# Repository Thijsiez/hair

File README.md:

# hair - Home Assistant IR blaster
The joke is that I'm bald :)

## :construction: WIP :construction:
This repo is currently a work-in-progress. I will add more information and documentation later.  
As long as this message is here, I'm open to suggestions but please do not assume anything is done or will work without issues.

## Versions
- [01](./hair-01) is a flawed prototype **DO NOT BUILD OR REFERENCE**
- [02](./hair-02) **WIP**

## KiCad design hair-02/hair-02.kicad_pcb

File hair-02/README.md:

# hair-02

The goal for 02 is to not need a USB-to-Serial interface chip like 01, lowering the total BOM cost. Another benefit of using the newer ESP32-C3 SoC, compared to the ESP8266, is that it uses the open source RISC-V instruction set.

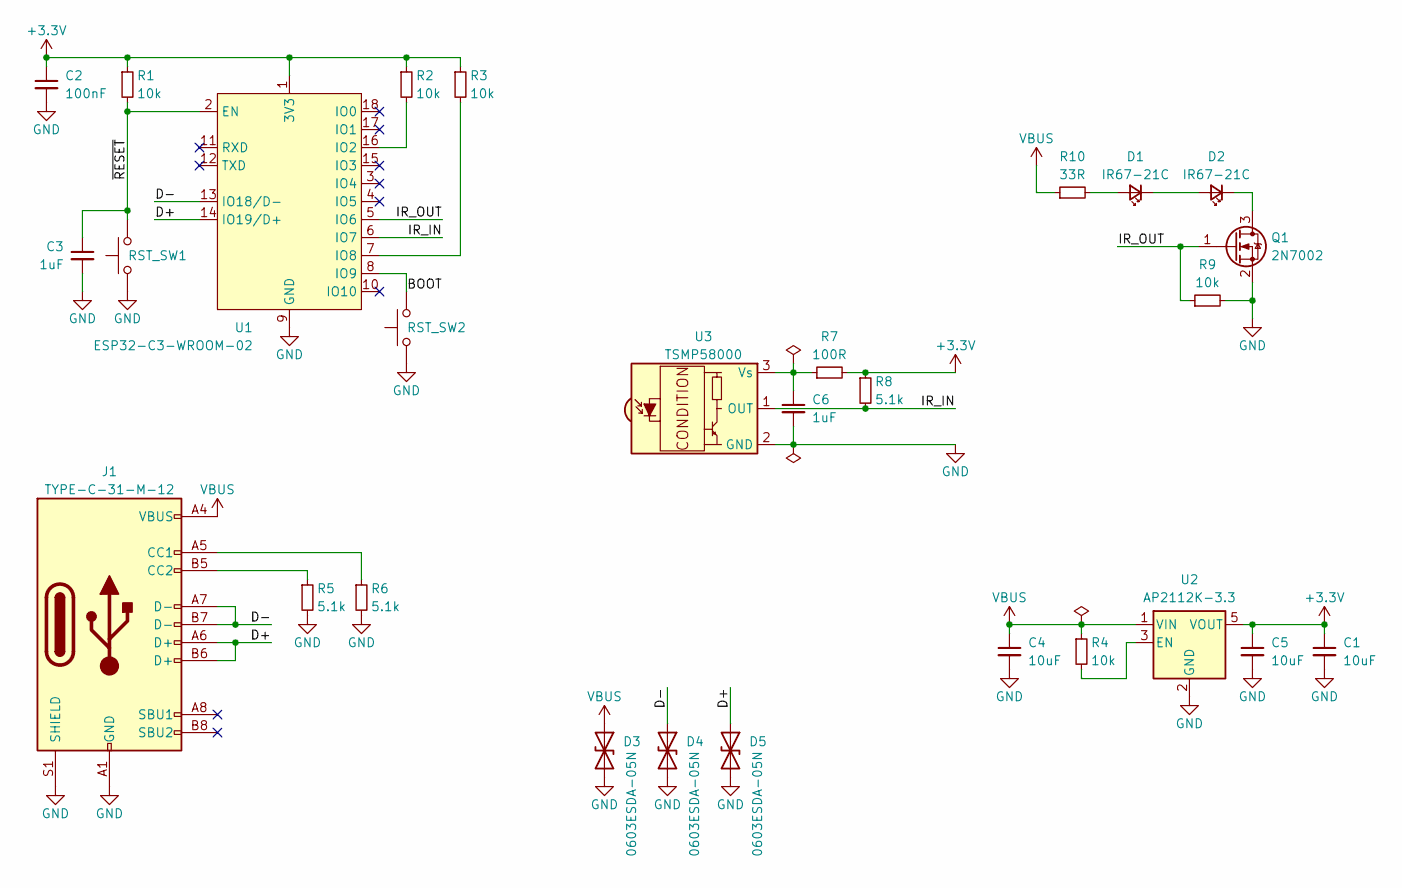
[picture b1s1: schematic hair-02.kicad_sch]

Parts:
C1, C4, C5: 10uF; C_1206_3216Metric; LCSC C13585
C2: 100nF; C_0603_1608Metric; LCSC C14663
C3, C6: 1uF; C_0805_2012Metric; LCSC C28323
D1, D2: IR67-21C; LED_Everlight_IR67-21C; LCSC C60109
D3, D4, D5: 0603ESDA-05N; D_0603_1608Metric; LCSC C316054
J1: TYPE-C-31-M-12; USB_C_Receptacle_HRO_TYPE-C-31-M-12; LCSC C165948
Q1: 2N7002; SOT-23; LCSC C414015
R1, R2, R3, R4, R9: 10k; R_0603_1608Metric; LCSC C25804
R5, R6, R8: 5.1k; R_0603_1608Metric; LCSC C23186
R7: 100R; R_0603_1608Metric; LCSC C22775
R10: 33R; R_1206_3216Metric; LCSC C144495
RST_SW1, RST_SW2: SKRK; SW_Push_SPST_NO_Alps_SKRK; LCSC C202388
U1: ESP32-C3-WROOM-02; LCSC C2934560
U2: AP2112K-3.3; SOT-23-5; LCSC C51118
U3: TSMP58000; Vishay_MINICAST-3Pin-SMD_ReverseMount; LCSC C511392

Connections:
+3V3: C1.1, C2.1, C5.1, R1.1, R2.1, R3.1, R7.2, R8.1, U1.1 (3V3), U2.5 (VOUT)
/BOOT: RST_SW2.2, U1.8 (IO9)
/D+: D5.1 (A1), J1.A6 (D+), J1.B6 (D+), U1.14 (IO19/D+)
/D-: D4.1 (A1), J1.A7 (D-), J1.B7 (D-), U1.13 (IO18/D-)
/IR_IN: R8.2, U1.6 (IO7), U3.1 (OUT)
/IR_OUT: Q1.1 (G), R9.1, U1.5 (IO6)
/~RESET: C3.1, R1.2, RST_SW1.2, U1.2 (EN)
GND: C1.2, C2.2, C3.2, C4.2, C5.2, C6.2, D3.2 (A2), D4.2 (A2), D5.2 (A2), J1.A1 (GND), J1.A12 (GND), J1.B1 (GND), J1.B12 (GND), J1.S1 (SHIELD), Q1.2 (S), R5.2, R6.2, R9.2, RST_SW1.1, RST_SW2.1, U1.9 (GND), U1.19 (GND), U2.2 (GND), U3.2 (GND)
unnamed: C6.1, R7.1, U3.3 (Vs)
unnamed: D1.1 (K), D2.2 (A)
unnamed: D1.2 (A), R10.2
unnamed: D2.1 (K), Q1.3 (D)
unnamed: J1.A5 (CC1), R6.1
unnamed: J1.B5 (CC2), R5.1
unnamed: R2.2, U1.16 (IO2)
unnamed: R3.2, U1.7 (IO8)
unnamed: R4.2, U2.3 (EN)
VBUS: C4.1, D3.1 (A1), J1.A4 (VBUS), J1.A9 (VBUS), J1.B4 (VBUS), J1.B9 (VBUS), R4.1, R10.1, U2.1 (VIN)

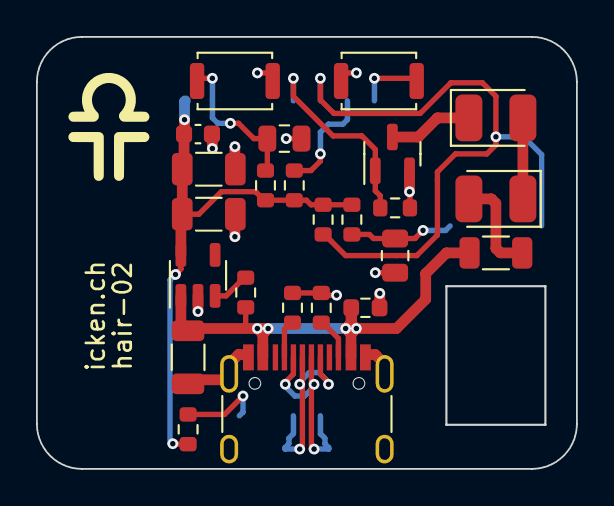
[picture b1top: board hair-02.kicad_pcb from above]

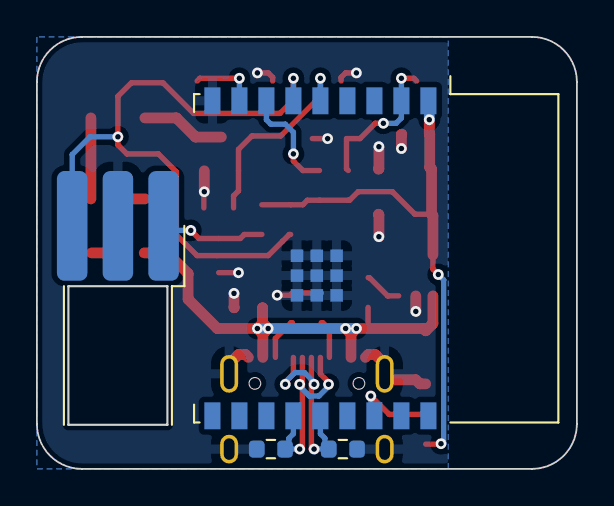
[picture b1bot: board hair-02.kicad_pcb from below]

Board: 2 copper layers, 30.0 x 24.0 mm, 28 parts (4 on the bottom side), 18 nets.

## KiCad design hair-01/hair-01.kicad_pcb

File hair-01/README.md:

# hair-01
**DO NOT USE OR REFERENCE THIS DESIGN, IT IS FLAWED AND I WILL NOT FIX IT!!**  
It's really only still here as a reference FOR ME so I don't make the same mistakes in the future.

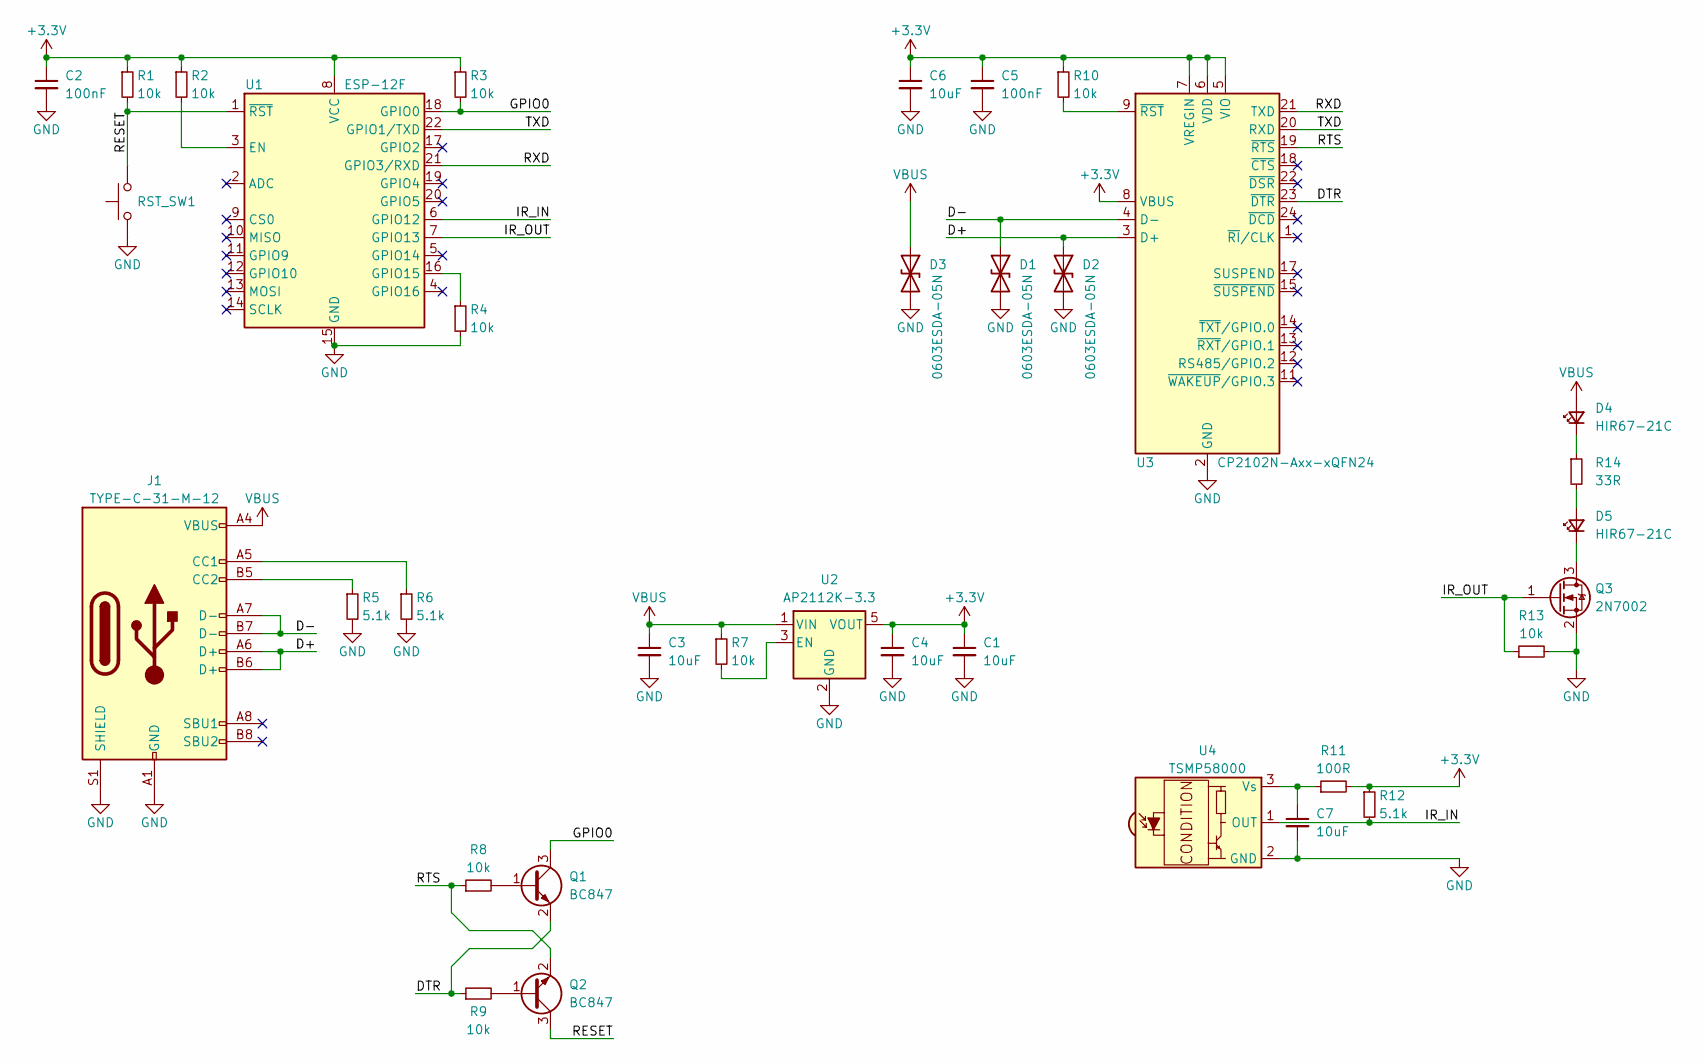
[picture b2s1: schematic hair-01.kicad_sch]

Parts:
C1, C3, C4, C6, C7: 10uF; C_1206_3216Metric; LCSC C13585
C2, C5: 100nF; C_0603_1608Metric; LCSC C14663
D1, D2, D3: 0603ESDA-05N; D_0603_1608Metric; LCSC C316054
D4, D5: HIR67-21C; LED_Everlight_HIR67-21C; LCSC C524055
J1: TYPE-C-31-M-12; USB_C_Receptacle_HRO_TYPE-C-31-M-12; LCSC C165948
Q1, Q2: BC847; SOT-23; LCSC C2150
Q3: 2N7002; SOT-23; LCSC C414015
R1, R2, R3, R4, R7, R8, R9, R10, R13: 10k; R_0603_1608Metric; LCSC C25804
R5, R6, R12: 5.1k; R_0603_1608Metric; LCSC C23186
R11: 100R; R_0603_1608Metric; LCSC C22775
R14: 33R; R_1206_3216Metric; LCSC C144495
RST_SW1: SW_Push; SW_Push_SPST_NO_Alps_SKRK; LCSC C202388
U1: ESP-12F; ESP-12E; LCSC C82891
U2: AP2112K-3.3; SOT-23-5; LCSC C51118
U3: CP2102N-Axx-xQFN24; QFN-24-1EP_4x4mm_P0.5mm_EP2.6x2.6mm; LCSC C969151
U4: TSMP58000; Vishay_MINICAST-3Pin-SMD; LCSC C511392

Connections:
+3V3: C1.1, C2.1, C4.1, C5.1, C6.1, R1.1, R2.1, R3.1, R10.1, R11.2, R12.1, U1.8 (VCC), U2.5 (VOUT), U3.5 (VIO), U3.6 (VDD), U3.7 (VREGIN), U3.8 (VBUS)
/D+: D2.1 (A1), J1.A6 (D+), J1.B6 (D+), U3.3 (D+)
/D-: D1.1 (A1), J1.A7 (D-), J1.B7 (D-), U3.4 (D-)
/DTR: Q1.2 (E), R9.1, U3.23 (~DTR)
/GPIO0: Q1.3 (C), R3.2, U1.18 (GPIO0)
/IR_IN: R12.2, U1.6 (GPIO12), U4.1 (OUT)
/IR_OUT: Q3.1 (G), R13.1, U1.7 (GPIO13)
/RESET: Q2.3 (C), R1.2, RST_SW1.2, U1.1 (~RST)
/RTS: Q2.2 (E), R8.1, U3.19 (~RTS)
/RXD: U1.21 (GPIO3/RXD), U3.21 (TXD)
/TXD: U1.22 (GPIO1/TXD), U3.20 (RXD)
GND: C1.2, C2.2, C3.2, C4.2, C5.2, C6.2, C7.2, D1.2 (A2), D2.2 (A2), D3.2 (A2), J1.A1 (GND), J1.A12 (GND), J1.B1 (GND), J1.B12 (GND), J1.S1 (SHIELD), Q3.2 (S), R4.2, R5.2, R6.2, R13.2, RST_SW1.1, U1.15 (GND), U2.2 (GND), U3.2 (GND), U3.25 (GND), U4.2 (GND)
unnamed: C7.1, R11.1, U4.3 (Vs)
unnamed: D4.1 (K), R14.1
unnamed: D5.1 (K), Q3.3 (D)
unnamed: D5.2 (A), R14.2
unnamed: J1.A5 (CC1), R6.1
unnamed: J1.B5 (CC2), R5.1
unnamed: Q1.1 (B), R8.2
unnamed: Q2.1 (B), R9.2
unnamed: R2.2, U1.3 (EN)
unnamed: R4.1, U1.16 (GPIO15)
unnamed: R7.2, U2.3 (EN)
unnamed: R10.2, U3.9 (~RST)
VBUS: C3.1, D3.1 (A1), D4.2 (A), J1.A4 (VBUS), J1.A9 (VBUS), J1.B4 (VBUS), J1.B9 (VBUS), R7.1, U2.1 (VIN)

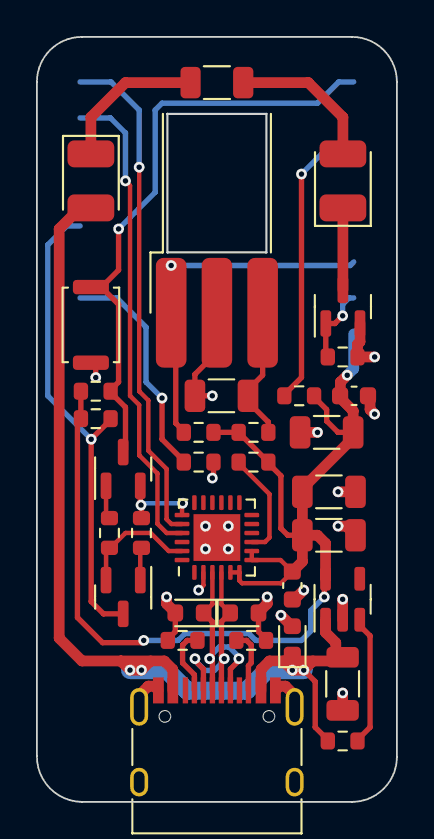
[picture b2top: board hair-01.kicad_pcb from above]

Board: 2 copper layers, 20.0 x 42.5 mm, 35 parts (1 on the bottom side), 25 nets.

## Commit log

2023-01-12 Add LICENSE
2023-01-26 hair-01: Add ESP-12F and USB-C receptacle
2023-01-26 hair-01: Add AP2112
2023-01-26 hair-01: Add reset button and auto-reset
2023-01-26 hair-01: Add CP2102N
2023-01-26 Add WIP notice
2023-01-26 hair-01: Add TSMP58000
2023-01-26 hair-01: Add IR output
2023-01-26 hair-01: Fix small naming mistake
2023-01-26 hair-01: Specify correct footprint for CP2102N
2023-01-26 hair-01: Rotate reset switch
2023-01-26 hair-01: Add footprints and start board layout
2023-01-26 hair-01: Replace reset button and more routing
2023-01-26 hair-01: More routing
2023-01-26 hair-01: Routing done
2023-01-26 hair-01: Add logo and name to silkscreen
2023-01-26 hair-01: Add gerbers
2023-01-26 hair-01: Add interactive BOM
2023-01-26 hair-01: Zip gerbers for JLCPCB ordering
2023-01-28 hair-01: Update README and add example BOM
2023-02-01 hair-01: Add exported STEP model
2023-02-18 hair-01: Found a mistake, added notice
2023-02-21 hair-02: Start designing 02
2023-02-22 hair-02: Component selection and schematic done
2023-02-22 hair-02: Add ESP32-C3-WROOM-02 footprint
2023-02-22 hair-02: Implement ESP32-C3-WROOM-02 footprint
2023-02-27 hair-02: WIP routing
2023-02-27 hair-02: WIP more routing
2023-03-01 hair-02: Routing done
    I'll sleep on it, see if I'm happy with my decisions later
2023-03-05 hair-02: Add gerbers and interactive BOM
2023-03-23 hair-02: Add assembly reference images
